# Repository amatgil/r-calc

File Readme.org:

* Calculadora de mà amb R

** Botons
- =p_=
- =q_=
- =d_=
- =_bern=
- =_binom=
- =_pois=
- =_nbinom=
- =_unif=
- =_norm=
- =0=
- =1=
- =2=
- =3=
- =4=
- =5=
- =6=
- =7=
- =8=
- =9=
- =+=
- =-=
- =*=
- =/=
- =^=
- =.=: Punt decimal
- =\==
- =Delete/Backspace=
- =Clear/On=
- =(=
- =)=
- =,=: Separador d'arguments de les funcions
- =Left=
- =Right=

** Layout preliminari
Legenda: =Normal Shifted=

Nove versió (ara amb =Shift=)
(TODO: Make shift be ternary instead of binary ({A, B, C}) to add extra distributions and constats (pi, e, phi))

| Shift   | <-       | ->     | Bksp/On Clear |
| 7 p     | 8 q      | 9  d   | *  ^          |
| 4 bern  | 5 pois   | 6 norm | - /           |
| 1 binom | 2 nbinom | 3 unif | +             |
| 0       | (  .     | ) ,    | =             |

*** Extra possibles
- `geom` 

** Altres infos
El protocol de communicació amb la LCD segurament tocarà escriure'l a mà. La veritat és que sona no-irònicament força divertit.

- Analyze elf size: https://github.com/jedrzejboczar/elf-size-analyze
- Hardware consideration for AVR in general, part 1: http://ww1.microchip.com/downloads/en/Appnotes/AN2519-AVR-Microcontroller-Hardware-Design-Considerations-00002519B.pdf
- Capacitors, from phasors: https://www.electronics-tutorials.ws/filter/filter_1.html
- Parasitic capacitance: https://circuitdigest.com/tutorial/understanding-esr-and-esl-in-capacitors
- (Capacitor search terms: "second order filter", "ESL" "ESR")

** Manufacturing options
*** Basic
| Nom           | Preu | Funció                                | Link                                                                                 |
|---------------+------+---------------------------------------+--------------------------------------------------------------------------------------|
| ATMEGA328P-PU | 2.7€ | La part que calcula de la calculadora | https://www.digikey.es/en/products/detail/microchip-technology/ATMEGA328P-PU/1914589 |
| LCD           | 10€  | Output                                |                                                                                      |
| Mòdul i2c     |      | Tradueix protocol per la LCD          |                                                                                      |
| 4*5 botons    | 5€   | Input                                 | https://www.digikey.es/en/products/detail/adafruit-industries-llc/1010/7244937       |

També cal un =usb to serial adapter= (so that it can get programmed)

*** Scalable
- Very cheap MCU
- LCD with i2c translator
-

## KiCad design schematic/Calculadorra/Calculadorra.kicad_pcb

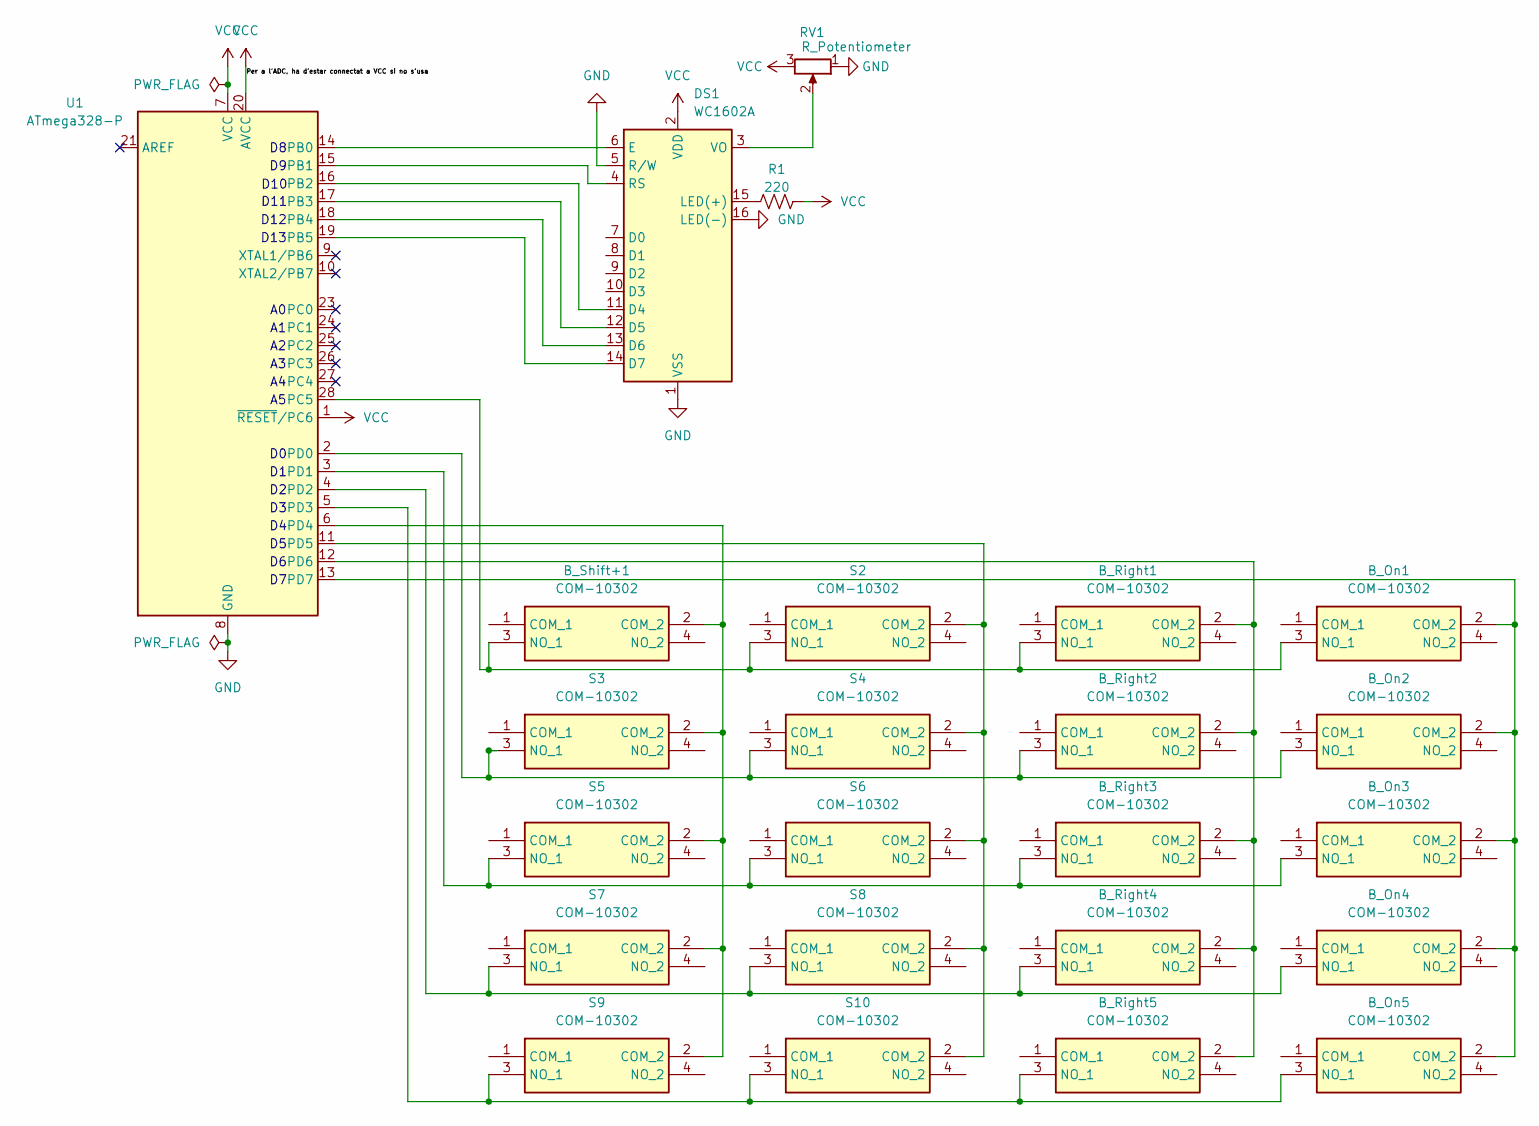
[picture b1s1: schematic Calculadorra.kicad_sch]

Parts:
B_On1, B_On2, B_On3, B_On4, B_On5: COM-10302; Button_COM10302; Mouser Part Number 474-COM-10302
B_Right1, B_Right2, B_Right3, B_Right4, B_Right5: COM-10302; Button_COM10302; Mouser Part Number 474-COM-10302
B_Shift+1: COM-10302; Button_COM10302; Mouser Part Number 474-COM-10302
DS1: WC1602A
R1: 220; R_LDR_4.9x4.2mm_P2.54mm_Vertical
RV1: R_Potentiometer; Potentiometer_ACP_CA6-VSMD_Vertical_Hole
S2, S3, S4, S5, S6, S7, S8, S9, S10: COM-10302; Button_COM10302; Mouser Part Number 474-COM-10302
U1: ATmega328-P; DIP-28_W7.62mm

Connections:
GND: DS1.1 (VSS), DS1.5 (R/W), DS1.16 (LED(-)), RV1.1, U1.8 (GND), U1.22 (GND)
unnamed: B_On1.2 (COM_2), B_On2.2 (COM_2), B_On3.2 (COM_2), B_On4.2 (COM_2), B_On5.2 (COM_2), U1.13 (PD7)
unnamed 2: B_On1.3 (NO_1), B_Right1.3 (NO_1), B_Shift+1.3 (NO_1), S2.3 (NO_1), U1.28 (PC5); also elsewhere on the board
unnamed: B_On2.3 (NO_1), B_Right2.3 (NO_1), S3.3 (NO_1), S4.3 (NO_1), U1.2 (PD0)
unnamed: B_On3.3 (NO_1), B_Right3.3 (NO_1), S5.3 (NO_1), S6.3 (NO_1), U1.3 (PD1)
unnamed: B_On4.3 (NO_1), B_Right4.3 (NO_1), S7.3 (NO_1), S8.3 (NO_1), U1.4 (PD2)
unnamed: B_On5.3 (NO_1), B_Right5.3 (NO_1), S9.3 (NO_1), S10.3 (NO_1), U1.5 (PD3)
unnamed: B_Right1.2 (COM_2), B_Right2.2 (COM_2), B_Right3.2 (COM_2), B_Right4.2 (COM_2), B_Right5.2 (COM_2), U1.12 (PD6)
unnamed 8: B_Shift+1.2 (COM_2), S3.2 (COM_2), S5.2 (COM_2), S7.2 (COM_2), S9.2 (COM_2), U1.6 (PD4); also elsewhere on the board
unnamed: DS1.11 (D4), U1.16 (PB2)
unnamed: DS1.12 (D5), U1.17 (PB3)
unnamed: DS1.13 (D6), U1.18 (PB4)
unnamed: DS1.14 (D7), U1.19 (PB5)
unnamed: DS1.6 (E), U1.14 (PB0)
unnamed: DS1.15 (LED(+)), R1.1
unnamed: DS1.4 (RS), U1.15 (PB1)
unnamed: DS1.3 (VO), RV1.2
unnamed: S2.2 (COM_2), S4.2 (COM_2), S6.2 (COM_2), S8.2 (COM_2), S10.2 (COM_2), U1.11 (PD5)
VCC: DS1.2 (VDD), R1.2, RV1.3, U1.1 (~RESET/PC6), U1.7 (VCC), U1.20 (AVCC)

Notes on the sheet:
D11
D13
D12
D10

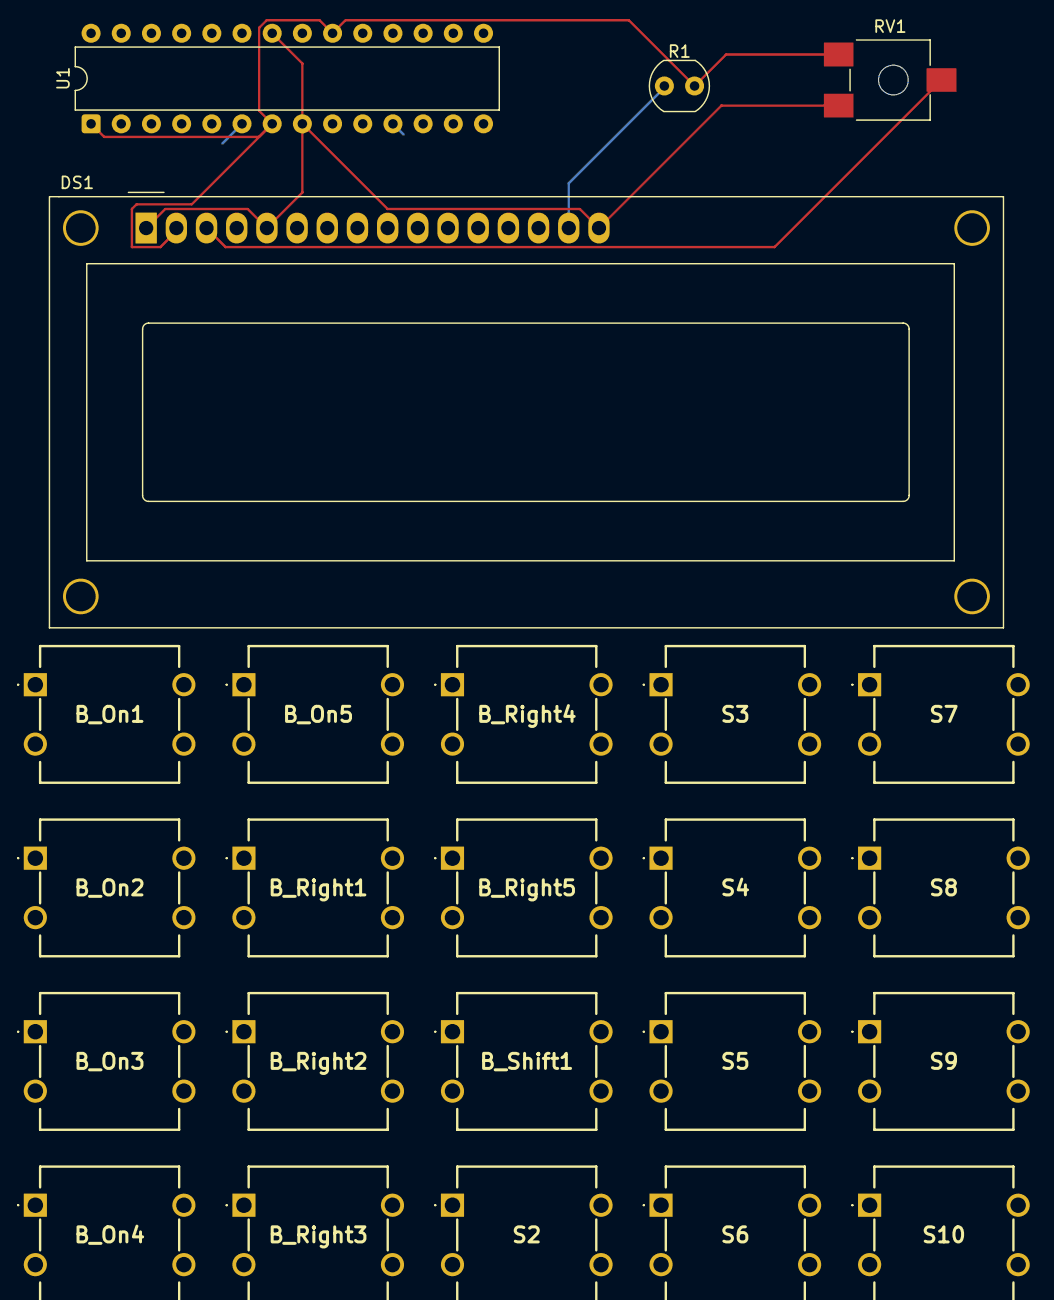
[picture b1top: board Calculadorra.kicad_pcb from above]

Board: 4 copper layers, 24 parts (0 on the bottom side), 19 nets.

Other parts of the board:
B_Shift1: COM-10302; Button_COM10302

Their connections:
unnamed 2: B_Shift1.3 (NO_1); also elsewhere on the board
unnamed 8: B_Shift1.2 (COM_2); also elsewhere on the board

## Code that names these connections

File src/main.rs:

#![cfg_attr(not(test), no_std)]
#![cfg_attr(not(test), no_main)]

use arduino_hal::{port::PinOps, prelude::*, *};
use hd44780_driver::{Cursor, CursorBlink, Display, DisplayMode};
use r_calc::{
    BufferType, Calculadora, Dist, Operacio, Paren, ShiftStatus, Token, VariantR, DISPLAY_HEIGHT,
    DISPLAY_WIDTH, LCD_INTERNAL_WIDTH, SCAN_MATRIX_HEIGHT, SCAN_MATRIX_WIDTH,
};
use ufmt::uwriteln;

//#[cfg(not(test))]
#[arduino_hal::entry]
fn main() -> ! {
    use arduino_hal::Delay;
    use hd44780_driver::HD44780;
    use r_calc::Enter;

    let dp = arduino_hal::Peripherals::take().unwrap();
    let pins = arduino_hal::pins!(dp);

    //let mut serial = arduino_hal::default_serial!(dp, pins, 57600);

    let mut calculadora = Calculadora::default();
    let mut held = false;

    // membrane pad
    let cols = [
        pins.d4.into_pull_up_input().downgrade(), // PD4
        pins.d5.into_pull_up_input().downgrade(), // PD5
        pins.d6.into_pull_up_input().downgrade(), // PD6
        pins.d7.into_pull_up_input().downgrade(), // PD7
    ];

    let mut rows = [
        pins.d3.into_output().downgrade(), // PD3
        pins.d2.into_output().downgrade(), // PD2
        pins.d1.into_output().downgrade(), // PD1
        pins.d0.into_output().downgrade(), // PD0
        pins.a5.into_output().downgrade(), // PC5
    ];

    // lcd
    let rs = pins.d9.into_output().downgrade();
    let en = pins.d8.into_output().downgrade();
    let d4 = pins.d10.into_output().downgrade();
    let d5 = pins.d11.into_output().downgrade();
    let d6 = pins.d12.into_output().downgrade();
    let d7 = pins.d13.into_output().downgrade();

    let mut delay = Delay::new();

    let mut lcd = HD44780::new_4bit(rs, en, d4, d5, d6, d7, &mut delay).unwrap();
    _ = lcd.reset(&mut delay);
    _ = lcd.clear(&mut delay);
    _ = lcd.set_cursor_visibility(Cursor::Visible, &mut delay);
    _ = lcd.set_cursor_blink(CursorBlink::On, &mut delay);

    let mut pressed: [bool; SCAN_MATRIX_HEIGHT * SCAN_MATRIX_WIDTH];

    loop {
        if !calculadora.is_cache_valid {
            calculadora.is_cache_valid = true;
            _ = lcd.reset(&mut delay);

            let inner = calculadora.display();
            let (top, bottom) = inner.split_at(DISPLAY_WIDTH);

            _ = lcd.set_cursor_pos(0, &mut delay);
            _ = lcd.write_bytes(top, &mut delay);
            _ = lcd.set_cursor_pos(LCD_INTERNAL_WIDTH as u8, &mut delay);
            _ = lcd.write_bytes(bottom, &mut delay);
            let lcd_cursor_pos = if calculadora.graphical_cursor >= DISPLAY_WIDTH {
                LCD_INTERNAL_WIDTH + (calculadora.graphical_cursor - DISPLAY_WIDTH)
            } else {
                calculadora.graphical_cursor
            };
            //uwriteln!(&mut serial, "REDRAWING {}", lcd_cursor_pos).unwrap_infallible();
            _ = lcd.set_cursor_pos(lcd_cursor_pos as u8, &mut delay);
            _ = match calculadora.shift_status {
                ShiftStatus::Si => lcd.set_cursor_blink(CursorBlink::On, &mut delay),
                ShiftStatus::No => lcd.set_cursor_blink(CursorBlink::Off, &mut delay),
            };
        }

        pressed = [false; SCAN_MATRIX_HEIGHT * SCAN_MATRIX_WIDTH];
        // read scan matrix
        for row in 0..SCAN_MATRIX_HEIGHT {
            rows[row].set_low();
            for col in 0..SCAN_MATRIX_WIDTH {
                if cols[col].is_low() {
                    pressed[row * SCAN_MATRIX_WIDTH + col] = true;
                }
            }
            rows[row].set_high();
        }

        // No pressing multiple keys allowed
        if pressed.map(|b| if b { 1 } else { 0 }).iter().sum::<Enter>() > 1 {
            continue;
        }

        let is_curr_pressed = pressed.iter().any(|&b| b);

        // If nothing is pressed, no need to change
        if let Some(pressed_idx) = pressed.iter().position(|b| *b) {
            match calculadora.currently_shown_buffer {
                BufferType::Tokens => {
                    use ShiftStatus as S;
                    if !held {
                        calculadora.is_cache_valid = false;
                        match (calculadora.shift_status, pressed_idx) {
                            (S::No, 0) => calculadora.add_token(Token::Digit(0)),
                            (S::Si, 0) => {}

                            (S::No, 1) => calculadora.add_token(Token::Paren(Paren::Open)),
                            (S::Si, 1) => calculadora.add_token(Token::DecimalPoint),

                            (S::No, 2) => calculadora.add_token(Token::Paren(Paren::Close)),
                            (S::Si, 2) => calculadora.add_token(Token::Comma),

                            (_, 3) => {
                                calculadora.compute();
                                calculadora.currently_shown_buffer = BufferType::Resultat;
                                _ = lcd.set_cursor_visibility(Cursor::Invisible, &mut delay);
                                _ = lcd.set_cursor_blink(CursorBlink::Off, &mut delay);
                            }
                            (S::No, 4) => calculadora.add_token(Token::Digit(1)),
                            (S::Si, 4) => calculadora.add_dist_tokens(Dist::Binom),

                            (S::No, 5) => calculadora.add_token(Token::Digit(2)),
                            (S::Si, 5) => calculadora.add_dist_tokens(Dist::NBinom),

                            (S::No, 6) => calculadora.add_token(Token::Digit(3)),
                            (S::Si, 6) => calculadora.add_dist_tokens(Dist::Uniforme),

                            (_, 7) => calculadora.add_token(Token::Op(Operacio::Add)),

                            (S::No, 8) => calculadora.add_token(Token::Digit(4)),
                            (S::Si, 8) => calculadora.add_dist_tokens(Dist::Bernoulli),

                            (S::No, 9) => calculadora.add_token(Token::Digit(5)),
                            (S::Si, 9) => calculadora.add_dist_tokens(Dist::Poisson),

                            (S::No, 10) => calculadora.add_token(Token::Digit(6)),
                            (S::Si, 10) => calculadora.add_dist_tokens(Dist::Normal),

                            (S::No, 11) => calculadora.add_token(Token::Op(Operacio::Sub)),
                            (S::Si, 11) => calculadora.add_token(Token::Op(Operacio::Div)),

                            (S::No, 12) => calculadora.add_token(Token::Digit(7)),
                            (S::Si, 12) => calculadora.add_token(Token::VariantR(VariantR::P)),

                            (S::No, 13) => calculadora.add_token(Token::Digit(8)),
                            (S::Si, 13) => calculadora.add_token(Token::VariantR(VariantR::Q)),

                            (S::No, 14) => calculadora.add_token(Token::Digit(9)),
                            (S::Si, 14) => calculadora.add_token(Token::VariantR(VariantR::D)),

                            (S::No, 15) => calculadora.add_token(Token::Op(Operacio::Mul)),
                            (S::Si, 15) => calculadora.add_token(Token::Op(Operacio::Pow)),

                            (_, 16) => calculadora.toggle_shift(),

                            (_, 17) => calculadora.cursor_back(),

                            (_, 18) => calculadora.cursor_advance(),

                            (S::No, 19) => calculadora.clear(),
                            (S::Si, 19) => calculadora.del_token(),

                            // Pressing a button with no defined Shift should reset shift
                            (S::Si, _unassigned_button) => calculadora.toggle_shift(),

                            _ => {} // unreachable if scan matrix is set up right
                        }
                    }
                }
                BufferType::Resultat => {
                    if !held && is_curr_pressed {
                        calculadora.is_cache_valid = false;
                        calculadora.currently_shown_buffer = BufferType::Tokens;

                        _ = lcd.set_cursor_visibility(Cursor::Visible, &mut delay);
                        _ = lcd.set_cursor_blink(CursorBlink::On, &mut delay);
                    } else {
                        held = false;
                    }
                }
            }
        }
        match (held, is_curr_pressed) {
            (true, false) => held = false,
            (false, true) => held = true,
            _ => {}
        }
    }
}

#[cfg(not(test))]
#[panic_handler]
fn panic(_: &core::panic::PanicInfo) -> ! {
    loop {}
}

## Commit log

2024-10-27 Init
2024-10-27 Change panic handling
2024-10-27 Rename Spec to Readme
2024-10-27 Readme is now in org-mode
2024-10-27 Update monospace to be =code=
2024-10-27 Update layout so it's 8*4+1 (aaa I need one extra button)
2024-11-01 Update to include Shift idea
2024-11-01 Brain-fart, whoops
2024-11-08 Way too many changes that should've been commmited incrementally
2024-11-08 It's alive!
2024-11-08 It compiles and runs on the board! Yay
2024-11-08 Make factorial a table lookup call
2024-11-08 It can now be ran and tested ergonomically
2024-11-09 We're using libm for math now
2024-11-09 Back and forth functions
2024-11-09 LCD SHOWS
2024-11-09 Integrated! Minor logic bugs, but we're underway
2024-11-09 Not constantly writing to it now
2024-11-10 Fixed deletion
2024-11-10 Added result displaying
2024-11-10 Abstract better
2024-11-10 Add "not yet implemented" text lmao
2024-11-11 Use the second line instead of missing text (ignore tokens for now)
2024-11-11 Add more flags that hyperoptimize binary size
2024-11-11 Add links and sources to README
2024-11-11 Avoid panic when displaying
2024-11-11 Pricing
2024-11-11 Add link
2024-11-11 Remove misc column
2024-11-11 Add shift internals
2024-11-11 Shift funcionality fully implemented, including button control
2024-11-11 Fixed shift, holding and added paren when dist is pressed
2024-11-11 Removed legacy readme part
2024-11-14 Operacio is now PartialOrd
2024-11-14 Started work on 'to postfix' function
2024-11-15 Only closing parens are missing for the shunting yard algorithm
2024-11-15 Flash size goes up by 1KB, woa
2024-11-15 Fix cursor not displaying when it was on the second line
2025-01-29 Add schematic
2025-02-06 Start move to 328p
2025-02-06 Fix scan matrix for 5x4
2025-02-06 Add arduino uno schematics to mega320p
2025-02-06 Add a couple of shift buttons
2025-02-06 Finish shift layer
2025-02-06 Add paren after variant
2025-02-06 Finish adding comma and period
2025-02-06 Add TODO to readme
2025-02-07 Pushed board specs (lmao i forgor)
2025-02-07 Propagate shunting yard stack errors
2025-02-07 Compress match arms for more readability
2025-02-07 Replace 'str but it's ascii' with '[u8]' (woo type system)
2025-02-12 nose lol
2025-02-12 No idea what changed
2025-02-12 lmaoaasjfusifhusidh
2025-02-13 Finished dnorm function
2025-02-14 Fix unrelated test
2025-02-26 Add, untested
2025-02-26 Add newton tests
2025-02-26 Disseny de la PCB i model 3D fet durant la Hacknight
2025-02-26 PCB amb nous botons, ja posarem díodes i cables en altres moments
